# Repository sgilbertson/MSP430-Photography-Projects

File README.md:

# MSP430-Photography-Projects
Personal MSP430 projects, mainly photography-related

Here will place source code for some of my personal MSP430 microcontroller projects, mainly related to photography.

They're not designed for general use, but if you're working with MSP430 processors perhaps you'll find some of the material helpful or interesting.

Pololu DRV8825 Adjustment
=========================

See [https://www.pololu.com/product/2133]

Procedure:
 * Install jumper pulling M0,M1,M2 all low, for full stepping, not micro-stepping
 * Do not connect a motor
 * Clip the red lead of a voltmeter to a small screwdriver
 * Clip the black lead to ground
 * Apply power
 * Adjust the trimpot on the DRV8825 until the voltmeter reads half the motor amps rating

For example, if the motor is rated for 1A, adjust until the meter reads 0.5V.

Sample Motors
-------------

These are some motors I found in nearby surplus stores.

Japan Servo KP35M2-035
 * 37 ohms
 * Internet sources suggest 500mA, implying 0.5*37=18.5V -- tune to 250mV
 * 1.8° per pulse (200 pulses per rev), but testing suggests 4x that -- 1Hz ~50 seconds per rev, 200H ~4rev/sec
 * Runs OK on 12V around 250mA
 * Wdg1 = blue/red, Wdg2 = white/yellow

Litton-Clifton Precision 11-SHBX-51KT H347
 * 16 Ohms
 * 0.312A -- tune to 161mV
 * 0.312*16=5V
 * 1.8° per pulse

Small geared motor ABYJ28-5V or 24BYJ28-5V
 * 10x gear-down
 * Therefore 0.18°/pulse
 * 70 ohms, 5V, so 5/70=71.4mA -- tune to 36mV, or use 5V supply and tune high
 * Loads of torque at 5V up to about 100Hz (5 seconds per rev)
 * Won't start above 150Hz.
 * Wdg1 = blue/yellow, Wdg2 = orange/pink

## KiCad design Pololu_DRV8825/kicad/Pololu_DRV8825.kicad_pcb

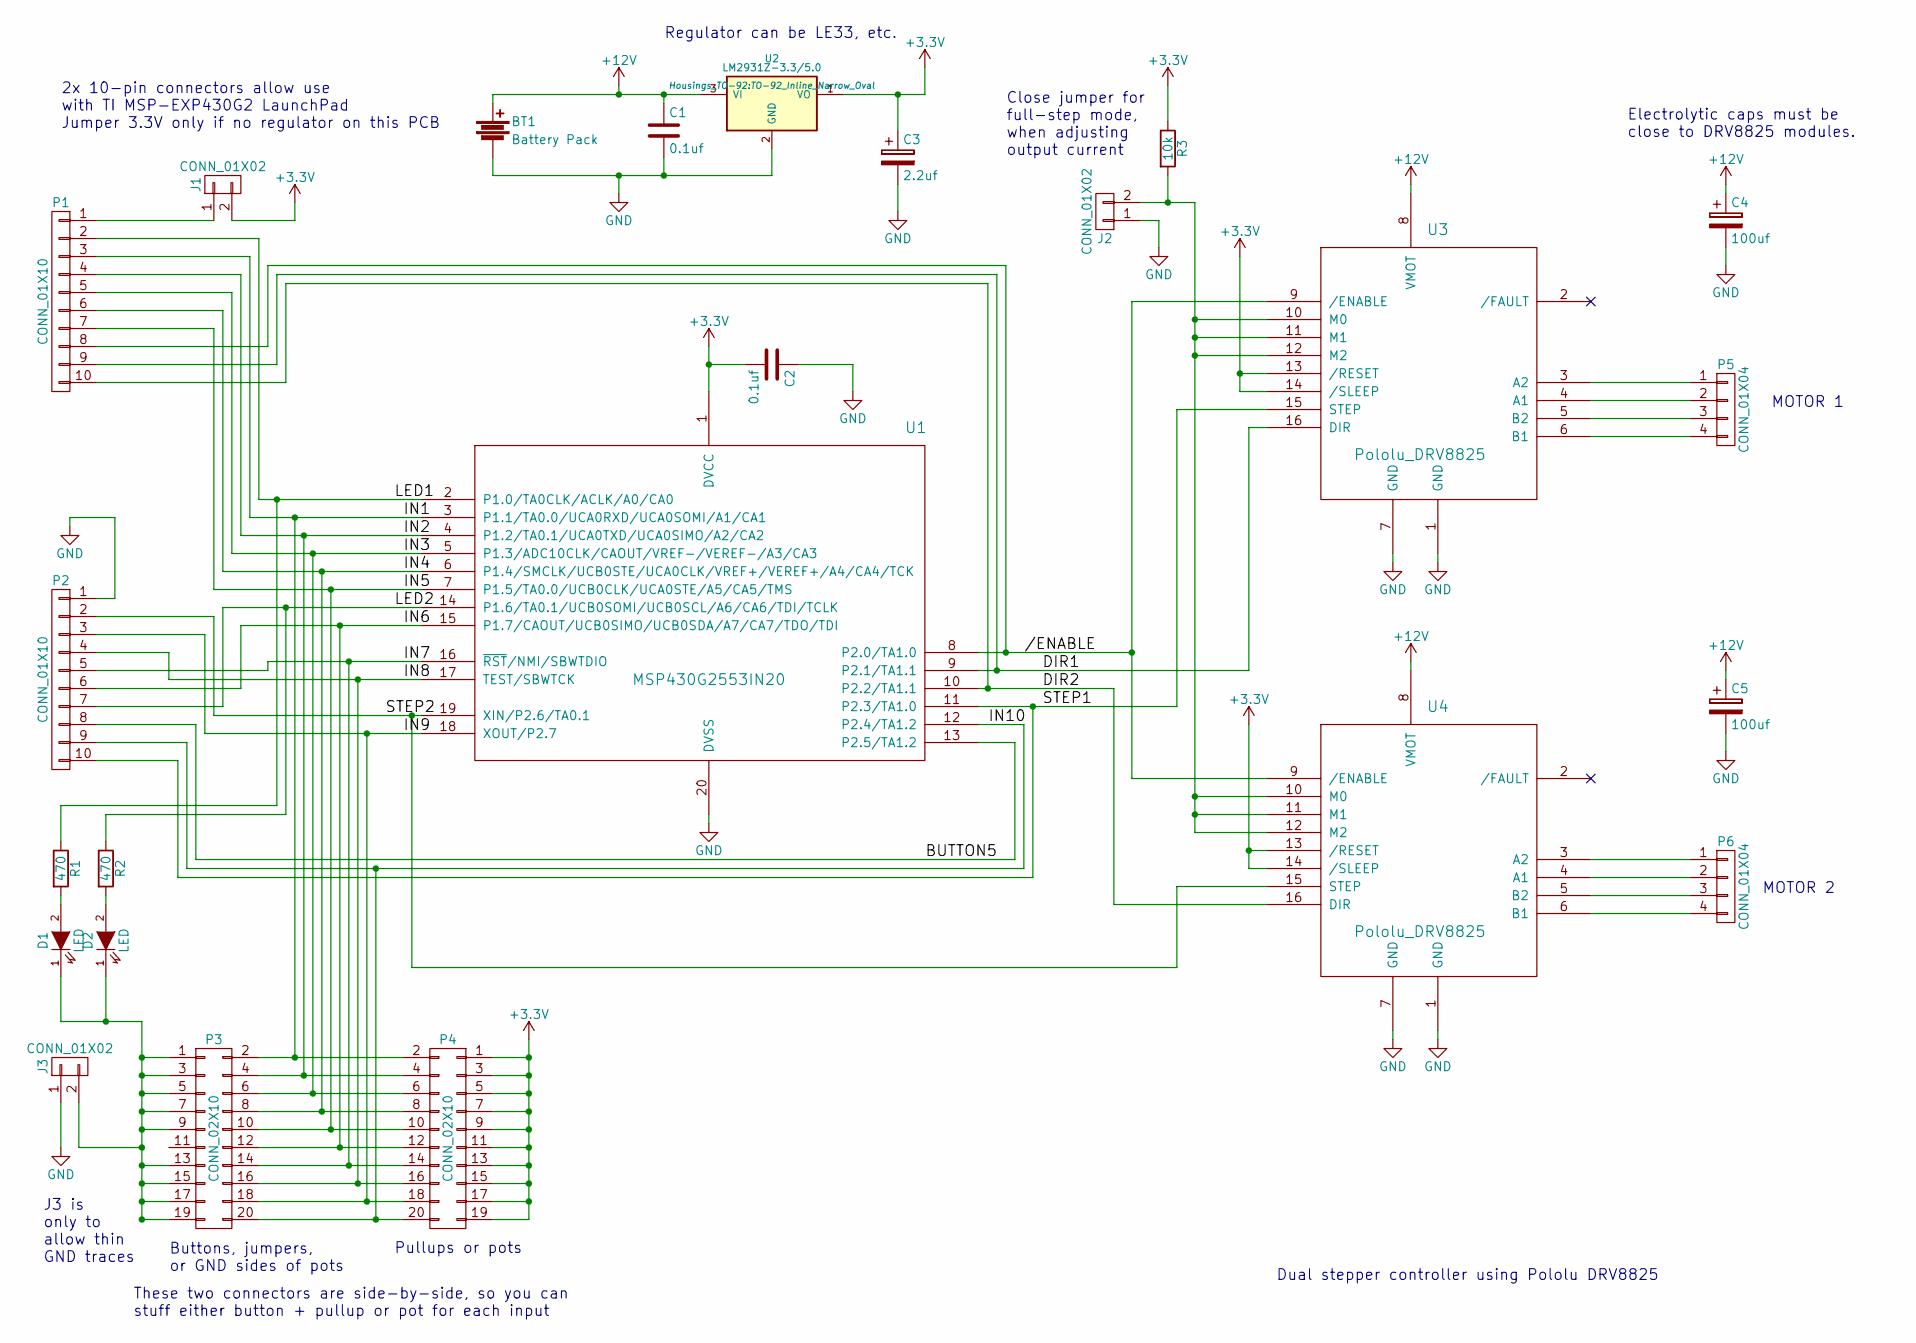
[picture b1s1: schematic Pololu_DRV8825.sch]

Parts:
BT1: Battery Pack; Pin_Header_Straight_1x02
C1, C2: 0.1uf; C_Disc_D6_P5
C3: 2.2uf; C_Disc_D3_P2.5
C4, C5: 100uf; C_Radial_D5_L6_P2.5
D1, D2: LED; LED-3MM
J1, J2, J3: CONN_01X02; Pin_Header_Straight_1x02
P1, P2: CONN_01X10; Pin_Header_Straight_1x10
P3, P4: CONN_02X10; Pin_Header_Straight_2x10
P5, P6: CONN_01X04; Pin_Header_Straight_1x04
R1, R2: 470; Resistor_Horizontal_RM15mm
R3: 10k; Resistor_Horizontal_RM15mm
U1: MSP430G2553IN20; DIP-20_W7.62mm
U2: LM2931Z-3.3/5.0; TO-92_Inline_Narrow_Oval
U3, U4: Pololu_DRV8825; DIP-16_W12.7mm

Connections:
+3V3: C2.2, C3.1, J1.2, P4.1, P4.3, P4.5, P4.7, P4.9, P4.11, P4.13, P4.15, P4.17, P4.19, R3.1, U1.1 (DVCC), U2.1 (VO), U3.13 (/RESET), U3.14 (/SLEEP), U4.13 (/RESET), U4.14 (/SLEEP)
+12V: BT1.1, C1.1, C4.1, C5.1, U2.3 (VI), U3.8 (VMOT), U4.8 (VMOT)
//ENABLE: P1.8, U1.8 (P2.0/TA1.0), U3.9 (/ENABLE), U4.9 (/ENABLE)
/BUTTON5: P2.8, U1.13 (P2.5/TA1.2)
/DIR1: P1.9, U1.9 (P2.1/TA1.1), U3.16 (DIR)
/DIR2: P1.10, U1.10 (P2.2/TA1.1), U4.16 (DIR)
/IN1: P1.3, P3.2, P4.2, U1.3 (P1.1/TA0.0/UCA0RXD/UCA0SOMI/A1/CA1)
/IN2: P1.4, P3.4, P4.4, U1.4 (P1.2/TA0.1/UCA0TXD/UCA0SIMO/A2/CA2)
/IN3: P1.5, P3.6, P4.6, U1.5 (P1.3/ADC10CLK/CAOUT/VREF-/VEREF-/A3/CA3)
/IN4: P1.6, P3.8, P4.8, U1.6 (P1.4/SMCLK/UCB0STE/UCA0CLK/VREF+/VEREF+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)
/IN5: P1.7, P3.10, P4.10, U1.7 (P1.5/TA0.0/UCB0CLK/UCA0STE/A5/CA5/TMS)
/IN6: P2.6, P3.12, P4.12, U1.15 (P1.7/CAOUT/UCB0SIMO/UCB0SDA/A7/CA7/TDO/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)
/IN7: P2.5, P3.14, P4.14, U1.16 (~RST~/NMI/SBWTDIO)
/IN8: P2.4, P3.16, P4.16, U1.17 (TEST/SBWTCK)
/IN9: P2.3, P3.18, P4.18, U1.18 (XOUT/P2.7)
/IN10: P2.9, P3.20, P4.20, U1.12 (P2.4/TA1.2)
/LED1: P1.2, R1.1, U1.2 (P1.0/TA0CLK/ACLK/A0/CA0)
/LED2: P2.7, R2.1, U1.14 (P1.6/TA0.1/UCB0SOMI/UCB0SCL/A6/CA6/TDI/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)
/STEP1: P2.10, U1.11 (P2.3/TA1.0), U3.15 (STEP)
/STEP2: P2.2, U1.19 (XIN/P2.6/TA0.1), U4.15 (STEP)
GND: BT1.2, C1.2, C2.1, C3.2, C4.2, C5.2, J2.1, J3.1, P2.1, U1.20 (DVSS), U2.2 (GND), U3.1 (GND), U3.7 (GND), U4.1 (GND), U4.7 (GND)
unnamed: D1.1 (K), D2.1 (K), J3.2, P3.1, P3.3, P3.5, P3.7, P3.9, P3.13, P3.15, P3.17, P3.19
unnamed: D1.2 (A), R1.2
unnamed: D2.2 (A), R2.2
unnamed: J1.1, P1.1
unnamed: J2.2, R3.2, U3.10 (M0), U3.11 (M1), U3.12 (M2), U4.10 (M0), U4.11 (M1), U4.12 (M2)
unnamed: P5.1, U3.3 (A2)
unnamed: P5.2, U3.4 (A1)
unnamed: P5.3, U3.5 (B2)
unnamed: P5.4, U3.6 (B1)
unnamed: P6.1, U4.3 (A2)
unnamed: P6.2, U4.4 (A1)
unnamed: P6.3, U4.5 (B2)
unnamed: P6.4, U4.6 (B1)

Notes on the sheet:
Dual stepper controller using Pololu DRV8825
2x 10-pin connectors allow use with TI MSP-EXP430G2 LaunchPad Jumper 3.3V only if no regulator on this PCB
Regulator can be LE33, etc.
Electrolytic caps must be close to DRV8825 modules.
Close jumper for full-step mode, when adjusting output current
MOTOR 1
MOTOR 2
Buttons, jumpers, or GND sides of pots
Pullups or pots
These two connectors are side-by-side, so you can stuff either button + pullup or pot for each input
J3 is only to allow thin GND traces

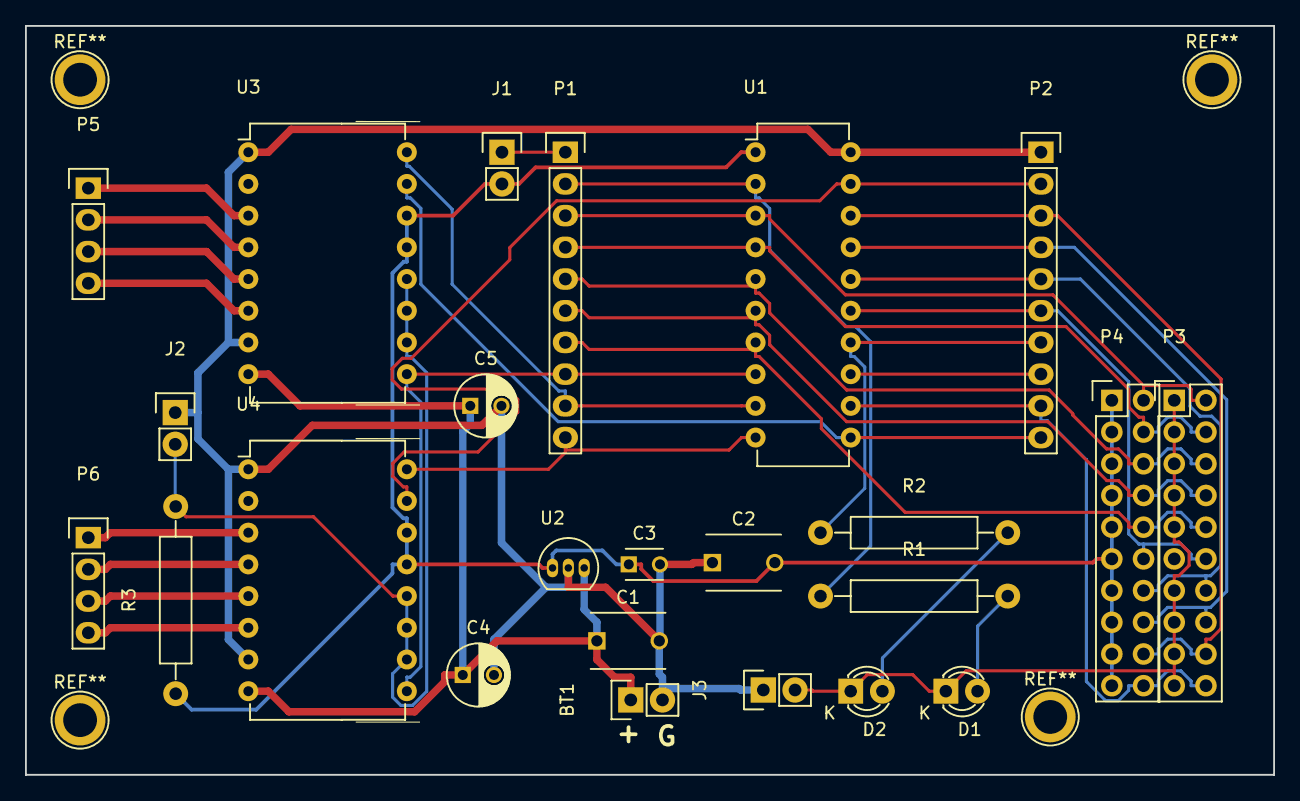
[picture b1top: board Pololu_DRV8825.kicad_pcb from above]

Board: 2 copper layers, 100.0 x 60.0 mm, 24 parts (0 on the bottom side), 34 nets.

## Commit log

2015-08-23 :octocat: Added .gitattributes & .gitignore files
2015-08-23 Initial commit of PWM1 project, which aims to drive an AC motor using a pair of power MOSFETs
2015-08-23 Initial commit of Stepper 1 project, which aims to control a stepper motor for motion time-lapse photography. Initially, the code is copied from PWM1.
2015-08-23 Stepper 1: Initial implementation of bipolar output to L293D or similar driver chip using 4 output pins, with the A+ and B+ states reflected on the LEDs.
2015-08-24 Stepper1 typo fix -- was writing step signals to the wrong port.
2015-08-24 Stepper1: Added variable speed using a potentiometer
    Potentiometer connects to the AD1 pin.
    Speed is limited to 500Hz ISR rate maximum.
    Minimum is roughly interval=65535
2015-09-04 Initial commit of dual Pololu DRV8825 stepper driver board
2015-09-04 DRV8825 - parts placed
2015-09-04 DRV8825 first routed board with mounting holes
2015-09-04 Ready for first manufacturing run
2015-09-11 Copied Stepper1 software project, to start DRV8825_app1
2015-09-11 Hacked together enough code to get some pulses going to the driver for motor 1. Pot on A1 controls the speed.
2015-09-26 Initial implementation of forward/reverse/stop buttons
2015-09-30 attempting to get direction buttons and dual speed pots working
2015-10-02 Got forward/reverse speed control apparently working, with buttons for forward, reverse and stop. Holding down the forward or reverse button obtains the speed setting from its respective ADC input.
2016-02-08 Added documentation of current-limit adjustment and some specific motors.
